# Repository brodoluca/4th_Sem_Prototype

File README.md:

# 4th Semester Prototype
Directory for the project developed by Group 1. Other information can be found in one of the following links:

[Trello](https://trello.com/b/kLbxPnjT/floatycar) [Google Slide](https://docs.google.com/presentation/d/1wOSUW8fcxm8XULRU-msCCsydfiLDzpCgxqQR87jBXo8/edit#slide=id.g8823499ab8_0_17)

Team members:

    Luca Brodo
    Kaan Tuna
    Gordan Konevski
    Vytaras Juraska
    Wiktor Kochanek

## Project Description
The project consists of an amphibious car with rescue capabilities. The prototype is based on an ambulance. The vehicle is able to drive on water and on all terrain.  

## Getting Started

#### Prerequisites

To run the simulation you need either a Windows Computer or a Linux computer with Ros installed

#### Install and build
In case of the Cpp simulation, what is needed is a simple compiler. Compile the program with required dependencies  found in the rep.
For Ros, you can just copy-paste the package on your workspace and run it.

## Versioning
    Ubuntu 18.04
    Ros Melodic
    Visual Studio 19
    Eclipse 2020-03 with Papyrus installed
    XCode 11.5

## License

We do not think that in the current situation the project, code in particular, is good enough to be used in a real situation. Please contact the owner of the repository if some parts of the code are going to be used.

## General Information

Folder hierarchy:

      -master
          --code
          --documentation
                ---Drawing                                  //contains the drawing of the model
                ---Preview                                  //some pictures of the model
                ---Requirements
                ---Solidworks                               //solidworks File
                ---Vehicle description
                ---General Diagram                          //system level diagrams
                ---SubSystem Specific diagrams
          --protocols
          --simulation
                ---Ros Simulation
                ---Cpp simulation

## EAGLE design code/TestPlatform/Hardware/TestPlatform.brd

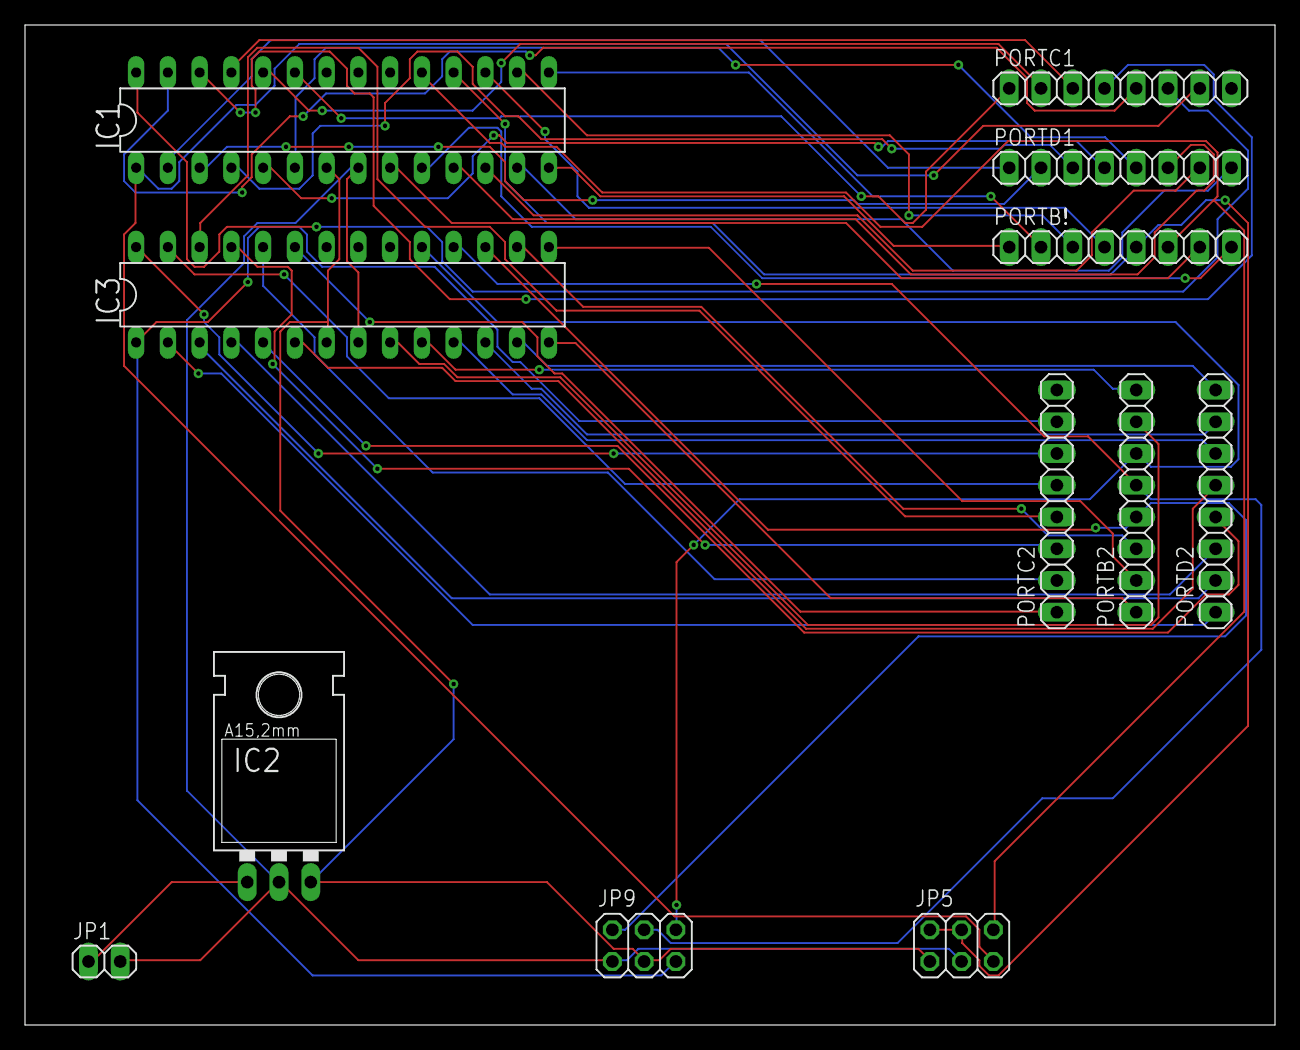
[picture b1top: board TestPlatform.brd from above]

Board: 2 copper layers, 100.0 x 80.0 mm, 12 parts (0 on the bottom side), 49 nets.

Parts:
IC1, IC3: ATMEGA168-20P; DIL28-3
IC2: 78XXL
JP1: 1X02
JP5, JP9: 2X03
PORTB2: 1X08
PORTB!: 1X08
PORTC1, PORTC2: 1X08
PORTD1, PORTD2: 1X08

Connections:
unnamed: IC1.8, IC2.GND, IC3.8, JP1.2, JP5.3, JP9.1
unnamed: IC2.IN, JP1.1
unnamed: IC1.2, PORTD1.1
unnamed: IC1.3, PORTD1.2
unnamed: IC1.4, PORTD1.3
unnamed: IC1.5, PORTD1.4
unnamed: IC1.6, PORTD1.5
unnamed: IC1.11, PORTD1.6
unnamed: IC1.12, PORTD1.7
unnamed: IC1.13, PORTD1.8
unnamed: IC1.14, PORTB!.1
unnamed: IC1.15, PORTB!.2
unnamed: IC1.16, PORTB!.3
unnamed: IC1.17, PORTB!.4
unnamed: IC1.18, JP5.2, JP5.4, PORTB!.5
unnamed: IC1.19, JP5.6, PORTB!.6
unnamed: IC1.9, PORTB!.7
unnamed: IC1.10, PORTB!.8
unnamed: IC1.23, PORTC1.1
unnamed: IC1.24, PORTC1.2
unnamed: IC1.25, PORTC1.3
unnamed: IC1.26, PORTC1.4
unnamed: IC1.27, PORTC1.5
unnamed: IC1.28, PORTC1.6
unnamed: IC1.1, JP5.5, PORTC1.7
unnamed: IC3.2, PORTD2.1
unnamed: IC3.3, PORTD2.2
unnamed: IC3.4, PORTD2.3
unnamed: IC3.5, PORTD2.4
unnamed: IC3.6, PORTD2.5
unnamed: IC3.11, PORTD2.6
unnamed: IC3.12, PORTD2.7
unnamed: IC3.13, PORTD2.8
unnamed: IC3.14, PORTB2.1
unnamed: IC3.15, PORTB2.2
unnamed: IC3.16, PORTB2.3
unnamed: IC3.17, JP9.2, PORTB2.4
unnamed: IC3.18, JP9.4, PORTB2.5
unnamed: IC3.19, JP9.6, PORTB2.6
unnamed: IC3.9, PORTB2.7
unnamed: IC3.10, PORTB2.8
unnamed: IC3.23, PORTC2.1
unnamed: IC3.24, PORTC2.2
unnamed: IC3.25, PORTC2.3
unnamed: IC3.26, PORTC2.4
unnamed: IC3.27, PORTC2.5
unnamed: IC3.28, PORTC2.6
unnamed: IC3.1, JP9.5, PORTC2.7
unnamed: IC1.7, IC2.OUT, IC3.7, JP5.1, JP9.3

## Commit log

2020-03-26 read.me
    er
2020-03-26 Rename READ.me to README.md
2020-04-16 Rename Development Agenda.md to Development Agenda
2020-04-19 Im trying
2020-04-19 Removing previous READ.me
2020-04-19 Removed car_sys folder
2020-04-19 Create Folder Protocols
2020-04-19 Adding today meeting
2020-04-19 ciao
2020-04-19 modified something
2020-04-19 tried
2020-04-19 changed
2020-04-19 getting started with git added
2020-04-19 I am Kaan
2020-04-19 changes in get started
2020-04-29 requirementDiagrama
2020-05-06 Create Code Folder and add arduino code
2020-05-06 Create Package Folder in code and copied SPI folder
2020-05-06 Commented SPI code
2020-05-07 New Code for SPi Raspi
2020-05-07 Some changes in the function
2020-05-07 Added new code for arduinoi, no error handling
2020-05-07 Port Manipulation, Code Cleanup
2020-05-13 Pictures of the car
2020-05-13 preview
2020-05-13 uploading my branch
2020-05-13 New protocol
2020-05-13 meeting 3
2020-05-17 Remove video
2020-05-17 functioning spi
2020-05-17 group task overview
2020-05-18 Simulation
2020-05-19 Tasks update
2020-05-19 Disciplines
2020-05-19 Update Tasks
2020-05-19 Updates on tasks and subs
2020-05-19 Subsystem diagrams
    Subsystem
2020-05-19 Updates subs diagrams
2020-05-19 Updates on tasks
2020-05-20 folder organization stuff
2020-05-20 Aff and signifiers
2020-05-20 changes on the vehicle description
2020-05-20 tasks updated
2020-05-21 Task update
2020-05-21 Subsistem modification
2020-05-21 Create LICENSE
2020-05-21 TaskUpdate
2020-05-21 Folder organization
2020-05-21 Old SPi file removed
2020-05-27 UltrasoundHandler
2020-05-27 Small changes for errors
2020-05-28 Added light sensor code
2020-05-28 redeability changes
2020-05-28 new diagram
2020-05-28 redeability issues
2020-05-28 changes on the variables name
2020-05-30 Added ranges to the code, tempor.
2020-06-03 new descrpition
2020-06-03 Added C++ simulation (only windows)
2020-06-05 working files for ultrasoundsens. for atmega
2020-06-05 Revision to make it platform indipendet
2020-06-05 comments added
2020-06-06 working libraries tested on Atmega 328p
2020-06-07 woking schematics
2020-06-08 buffer implentation
2020-06-08 Added test platform schematics
2020-06-11 new_model1
2020-06-11 sliced model
2020-06-14 added simulink model
2020-06-15 directory refactoring and added new working codes
2020-06-16 read. adj.
2020-06-17 defined position frequencies
2020-06-17 new flame sensor added
2020-06-20 definitive model
2020-06-21 Removed pictures of the car
2020-06-21 temporary file
2020-06-21 Status property changed
2020-06-21 New obstacle detection
2020-06-21 Added Obstacle state machine, aligned images
2020-06-21 new comments added
2020-06-21 new PCB
2020-06-22 temporary refactoring
